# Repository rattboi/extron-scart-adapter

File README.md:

Extron Scart Adapter projects
=============================

Extron Input Adapter
--------------------

[Extron-Input README](extron-input/README.md)

This board should plug into an extron crosspoint input, and has the following features:

1) Female Scart input
1) JST header to Phoenix adapter (cheap)
1) Sense header to determine if connected cable is "active"
1) Selectable LM1881 Sync Stripper for sync on composite video / sync on luma

Extron Output Adapter
--------------------

[Extron-Output README](extron-output/README.md)

This board should plug into an extron crosspoint output, and has the following features:

1) Female Scart output
1) JST header to Phoenix adapter (cheap)
1) Selectable termination resistor for 75 ohm or TTL level sync output

Extron SCART Autoswitcher
-------------------------

[Autoswitcher README](esp32-switcher/README.md)

This board plugs into the serial port on an Extron crosspoint, and works together with the input cards to determine which input has be most-recently powered on, and automatically switches to that input.

Simple Scart Adapter (DEPRECATED)
---------------------------------

This board was my first attempt, and it turned out to not be workable. I'm leaving it for posterity, but you shouldn't use it.
The spacing is way off for a Crosspoint. I based the measurements on an Extron System 5CR Plus, which has narrower spacing between BNC connectors.

License
-------

These projects are licensed under CERN Open Hardware Licence v1.2

This is a work-in-progress as well, as I believe I'm missing the attribution on the boards. My intent is to license them properly.

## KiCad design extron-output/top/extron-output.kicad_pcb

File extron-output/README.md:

Extron SCART Output Adapter
==========================

PCB Renders
===========

## Front

## Back

3D Renders
==========

## Top

## Front

## Side

BOM 
===

| Item | Qty | Reference(s)     | Value      | Footprint                                                   | Datasheet                                                                                                            |
|------|-----|------------------|------------|-------------------------------------------------------------|----------------------------------------------------------------------------------------------------------------------|
| 1    | 1   | J1               | SCART-F    | extron-input:SCART_F_RA, ~                                  | https://console5.com/store/female-scart-jp21-through-hole-pcb-mount-21-pin-connector-right-angle.html                |
| 2    | 1   | J2/J11           | RED        | extron-input:rca_boom, ~                                    | https://lcsc.com/product-detail/AV-Connectors_AV-5_C18080.html                                                       |
| 3    | 1   | J3               | GREEN      | extron-input:rca_boom, ~                                    | https://lcsc.com/product-detail/AV-Connectors_AV-5_C18080.html                                                       |
| 4    | 1   | J4/J12           | BLUE       | extron-input:rca_boom, ~                                    | https://lcsc.com/product-detail/AV-Connectors_AV-5_C18080.html                                                       |
| 5    | 1   | J5/J13           | SYNC       | extron-input:rca_boom, ~                                    | https://lcsc.com/product-detail/AV-Connectors_AV-5_C18080.html                                                       |
| 6    | 1   | R1               | 470        | R_Axial_DIN0204_L3.6mm D1.6mm_P1.90mm_Vertical              | https://lcsc.com/product-detail/Metal-Film-Resistor-TH_470R-471-5_C176518.html                                       |
| 7    | 1   | J6               | PHOENIX    | Connector_JST:JST_XH_S03B XH-A_1x03_P2.50mm_Horizontal,~    | https://lcsc.com/product-detail/Wire-To-Board-Wire-To-Wire-Connector_JST-Sales-America_S3B-XH-A-LF-SN_JST-Sales-America-S3B-XH-A-LF-SN_C157928.html |
| 8    | 1   | SW1              | CSYNC      | 3x1 Pin Header                                              | (fill me in)                                                                                                         |

LCSC     Sub-total: __$6.76__ for everything for 10x boards (plus lots of spare parts)
Console5 Sub-total: __$14.90__ for RA Female SCART connectors
BOM Total: __$21.66__ for 10x boards

You'll want 5x of the top boards and 5x of the bottom boards
PCBs: __$4 for 5__ top, __$4 for 5__ bottom, plus $6 for slower shipping = __$14__

Total board Costs for 10: $21.66+14 = $35.66 =  $3.57 each (pretty cheap)

Other Supporting Parts 
======================

Phoenix adapter (for audio)
---------------------------

I've respun db_electronics' Phoenix RCA plug board to use JST headers: https://github.com/rattboi/phoenix-audio-adapter-kicad/tree/jst-xh/

$5 for 10x more boards on JLCPCB order, and $0.89 for JST headers

__$5.89__ for 10x populated boards = __$0.59 each__

JST cables (connect input audio to phoenix board)
----------
https://www.amazon.com/gp/product/B07HRMWVK9/

__$8 for 10__(need to find a better source)

BNC M to RCA M Plug Adapters
---------------
https://www.amazon.com/gp/product/B005C2KA88/

$5.39 for 10

__$21.56 for 40__ (4x per board, 10 boards)

Alternative: 

https://www.amazon.com/gp/product/B01H1A4QAQ/

$6.42 for 10

$25.68 for 40

10x board Total
===============
10x board + phoenix + cables + adapters: $36 + $6 + $8 + $22 = __~$72__

__$7.20 each, all parts, shipped__

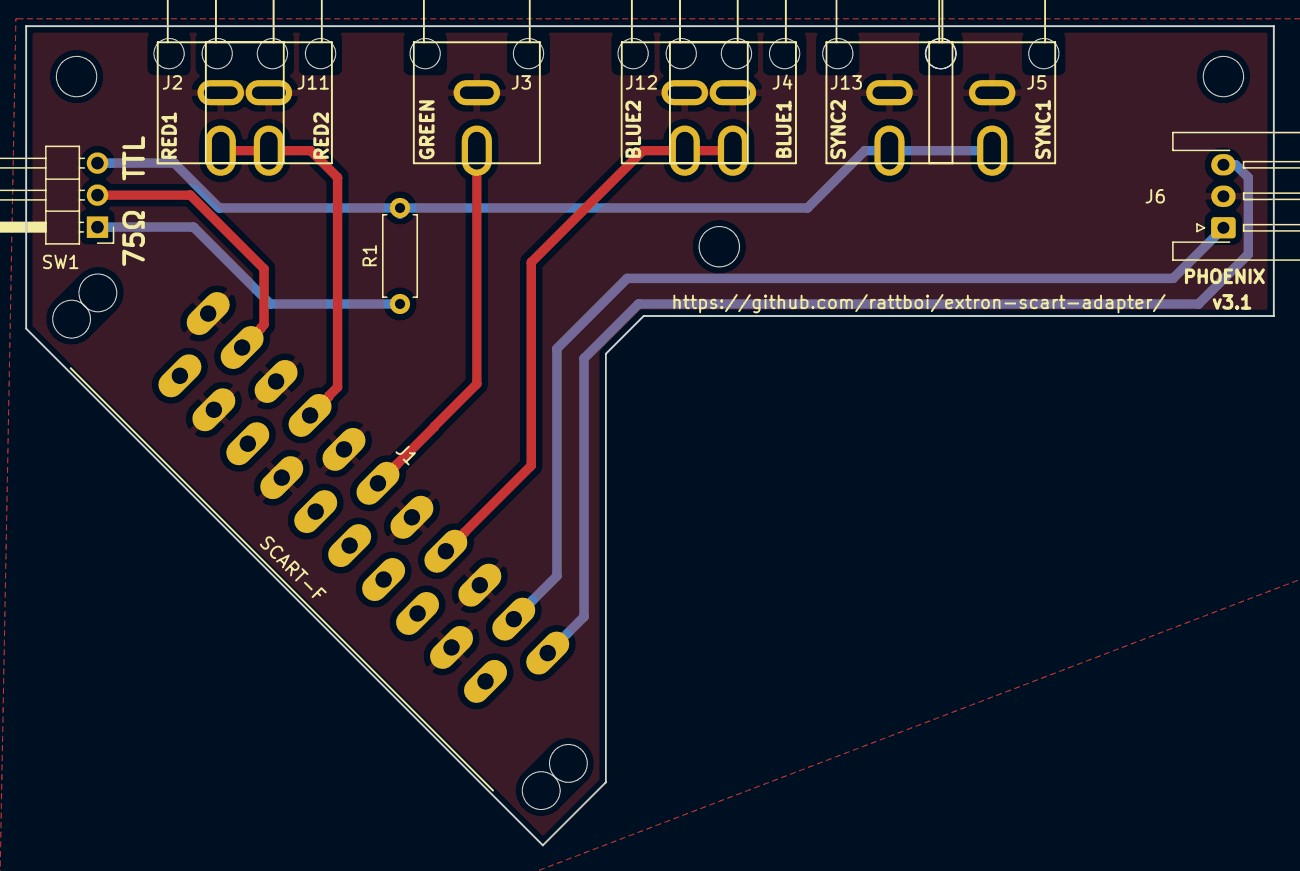
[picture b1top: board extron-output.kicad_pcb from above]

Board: 2 copper layers, 99.0 x 65.0 mm, 14 parts (0 on the bottom side), 9 nets.

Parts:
J1: SCART-F; SCART_F_RA
J2: RED1; rca_combined
J3: GREEN; rca_combined
J4: BLUE1; rca_combined
J5: SYNC1; rca_combined
J6: PHOENIX; JST_XH_S3B-XH-A-1_1x03_P2.50mm_Horizontal
J8, J9, J10: Conn_01x01; MountingHole_3.2mm_M3
J11: RED2; rca_combined
J12: BLUE2; rca_combined
J13: SYNC2; rca_combined
R1: 470; R_Axial_DIN0207_L6.3mm_D2.5mm_P7.62mm_Horizontal
SW1: SW_SPDT; PinHeader_1x03_P2.54mm_Horizontal

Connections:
BLUE: J1.7, J4.2, J12.2
GND: J1.4, J1.5, J1.9, J1.13, J1.14, J1.17, J1.18, J1.21, J2.1, J3.1, J4.1, J5.1, J6.2, J11.1, J12.1, J13.1
GREEN: J1.11, J3.2
unnamed: J1.1, J6.3
unnamed: J1.3, J6.1
unnamed: J1.19, SW1.2
unnamed: R1.1, SW1.1
RED: J1.15, J2.2, J11.2
SYNC: J5.2, J13.2, R1.2, SW1.3

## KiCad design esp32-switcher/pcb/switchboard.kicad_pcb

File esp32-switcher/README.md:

Extron SCART Autoswitcher
=========================

This board, in conjunction with a HiLetGo ESP-E32 development board, can be used to sense input changes from the Extron Input adapters, and use that information to automatically switch to the most recently turned-on input.

Each input board has a sense port, which you connect to the autoswitch board via a JST XH cable. The board then plugs into your extron either via straight-through M-F serial cable (not null modem), or by directly mounting the board onto the port. The ESP32 also needs external power, which can be supplied by any 5V USB charger that you may have laying around.

PCB
===

3D Renders
==========

PCB Renders
===========

BOM
===========
| Item  | Qty | Reference(s)     | Value      | Footprint                                                   | Datasheet                                                                                                            |
|-------|-----|------------------|------------|-------------------------------------------------------------|----------------------------------------------------------------------------------------------------------------------|
| 1     |   1 | U1               | ESP32      | hiletgo-e32:HILETGO-E32                                     |  https://www.amazon.com/gp/product/B0718T232Z/ref=ppx_yo_dt_b_search_asin_title?ie=UTF8&psc=1                        |
| 2     |   1 | J13/J16          | RS232      | Connector_PinSocket_2.54mm:PinSocket_1x04_P2.54mm_Vertical  |  https://www.amazon.com/gp/product/B00OPU2QJ4/ref=ppx_yo_dt_b_asin_title_o02_s00?ie=UTF8&psc=1                       |
| 3     |  14 | J1-12,14,15      | JST-XH RA  | Connector_JST:JST_XH_B2B-XH-AM_1x02_P2.50mm_Vertical        |                                                                                                                      |

Notes:
* You only need one RS232 TTL Converter. There's two spots (J13 or J16) on the board to place it, depending on what orientation you want your switchboard to be.
* You can skip J14/J15 for now. They are WIP to chain together switchboards for cascading multiple Extrons
* If you don't want the ESP32 to be permanently soldered to the switchboard, you can use pin header for the two rows of pins where the ESP32 plugs in.
* I would recommend directly soldering the RS232 in place for stability, but you could use pin header there as well.

Code
====

The code for the autoswitcher is currently in micropython. The basic steps involved are as follows to get the board going.

1) Install any driver you may need for the usb->serial built into the ESP32. This is the CP2102 driver, and necessary for Windows and macOS. Linux comes with this driver pre-installed.

2) Plug the ESP32 into your computer, and find the serial device.
  This is straightforward in Linux/macOS, as it appears as /dev/ttyUSB0 or something close to that. I'm not actually sure what this looks like in windows.

3) Install the following programs to interact with the ESP32: esptool.py and ampy.
  esptool.py will allow you to flash micropython onto your ESP32
  ampy will allow you to move the boot code from this repo onto your ESP32 to be executed by micropython

4) Install micropython, some current revision.
  I'm not going to go through all the steps for this, but on Linux it looks something like `sudo esptool --chip esp32 -p /dev/ttyUSB0 write_flash -z 0x1000 ~/Downloads/esp32-20190328-v1.10-243-g92149c8a7.bin`
  `
5) Move the boot code over after micropython is installed
  `ampy -p /dev/ttyUSB0 put code/boot.py`

You're done now. Plug everything in. J1 -> Input 1, J2 -> Input 2, etc.

Congrats, now you have autoswitching power!

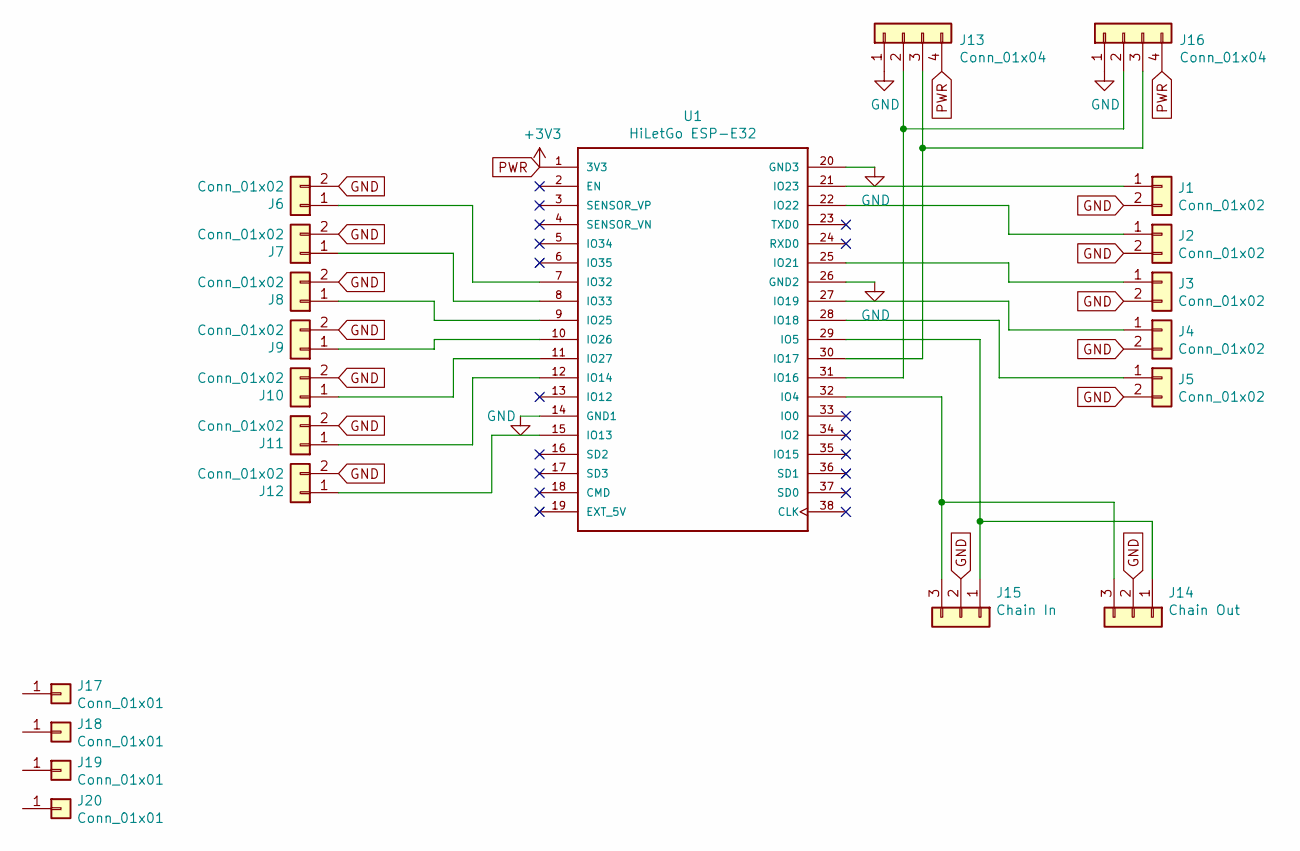
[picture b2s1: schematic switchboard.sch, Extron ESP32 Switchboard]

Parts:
J1, J2, J3, J4, J5, J6, J7, J8, J9, J10, J11, J12: Conn_01x02; JST_XH_B2B-XH-AM_1x02_P2.50mm_Vertical
J13, J16: Conn_01x04; PinSocket_1x04_P2.54mm_Vertical
J14: Chain Out; JST_XH_B3B-XH-AM_1x03_P2.50mm_Vertical
J15: Chain In; JST_XH_B3B-XH-AM_1x03_P2.50mm_Vertical
J17, J18, J19, J20: Conn_01x01; MountingHole_3.2mm_M3
U1: HiLetGo ESP-E32; HILETGO-E32

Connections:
GND: J1.2, J2.2, J3.2, J4.2, J5.2, J6.2, J7.2, J8.2, J9.2, J10.2, J11.2, J12.2, J13.1, J14.2, J15.2, J16.1, U1.14 (GND1), U1.20 (GND3), U1.26 (GND2)
unnamed: J1.1, U1.21 (IO23)
unnamed: J2.1, U1.22 (IO22)
unnamed: J3.1, U1.25 (IO21)
unnamed: J4.1, U1.27 (IO19)
unnamed: J5.1, U1.28 (IO18)
unnamed: J6.1, U1.7 (IO32)
unnamed: J7.1, U1.8 (IO33)
unnamed: J8.1, U1.9 (IO25)
unnamed: J9.1, U1.10 (IO26)
unnamed: J10.1, U1.11 (IO27)
unnamed: J11.1, U1.12 (IO14)
unnamed: J12.1, U1.15 (IO13)
unnamed: J13.2, J16.2, U1.31 (IO16)
unnamed: J13.3, J16.3, U1.30 (IO17)
unnamed: J14.1, J15.1, U1.29 (IO5)
unnamed: J14.3, J15.3, U1.32 (IO4)
PWR: J13.4, J16.4, U1.1 (3V3)

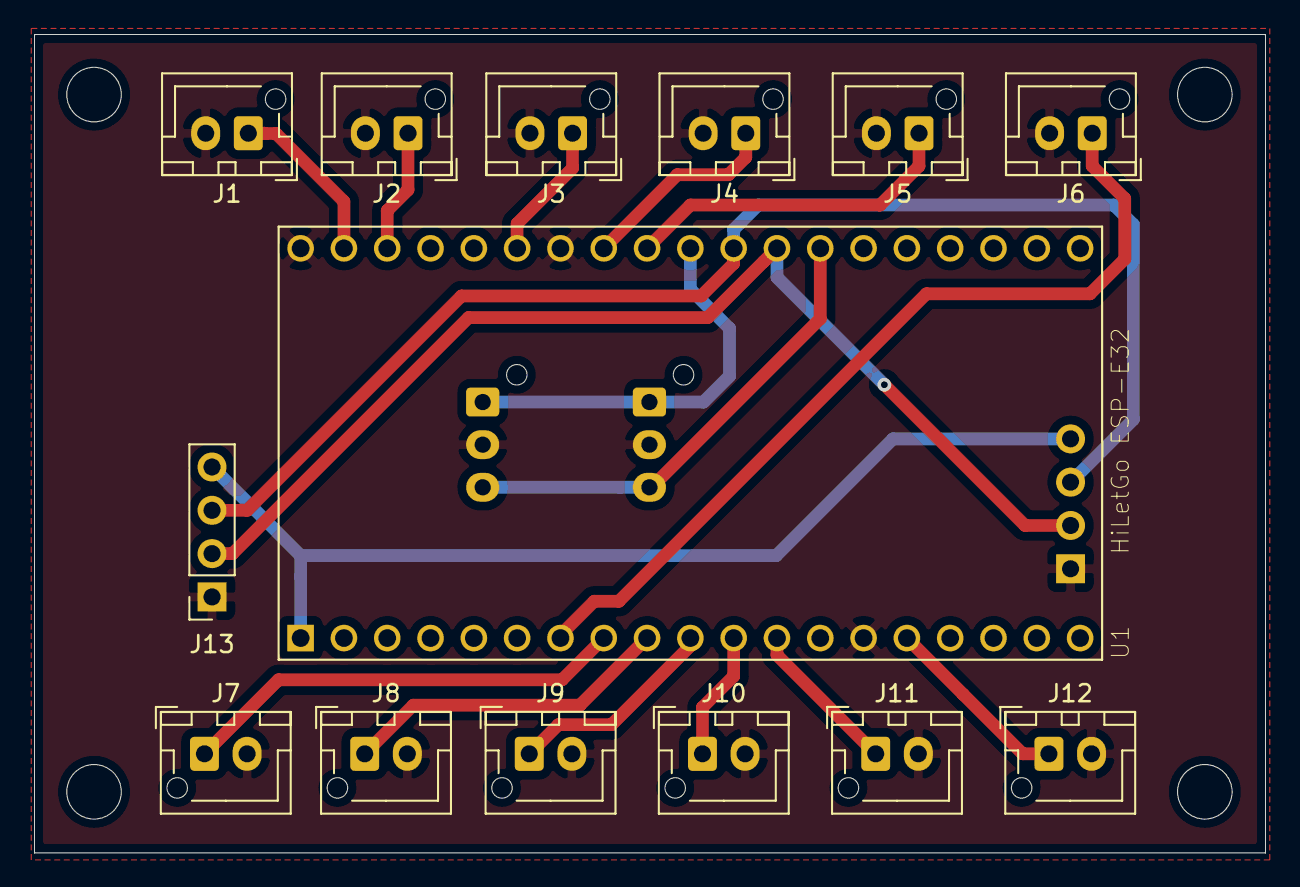
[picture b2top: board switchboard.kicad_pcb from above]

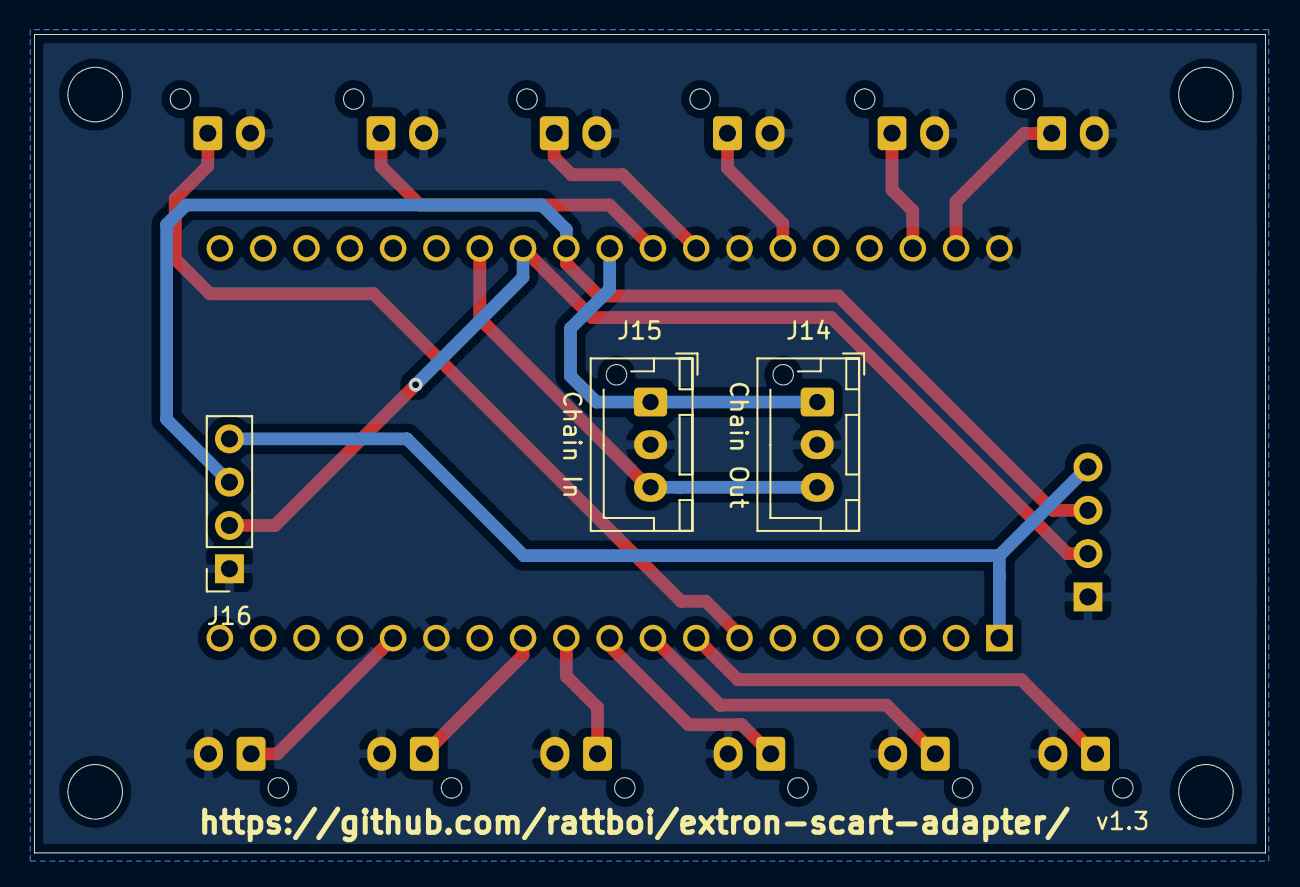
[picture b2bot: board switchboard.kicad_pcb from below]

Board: 2 copper layers, 72.2 x 48.0 mm, 21 parts (3 on the bottom side), 18 nets.

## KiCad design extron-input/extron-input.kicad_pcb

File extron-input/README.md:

Extron SCART Input adapter
==========================

The Extron SCART Input adapters are designed to be inserted into an Extron Crosspoint input vertically, using BNC->RCA male adapters to mate with the adapter card's RCA female jacks. There are two supported BNC spacings, one that is looser (older Extrons) and one that is tighter (newer Extrons). When you assemble your card, you use the correct RCA spacing to support your Extron. The looser spacing is labeled RED1/GREEN/BLUE1/SYNC1, while the tighter spacing is labeled RED2/GREEN/BLUE2/SYNC2. You'll notice that GREEN is shared between the two spacings.

Below, you will notice that there is a design for a 'top' card and a 'bottom' card. This was required in order to get the cards close enough together horizontally (from the perspective of the Extron). The SCART heads are large and for the newer Extron spacing, the BNC spacing is just too tight to have the SCART heads stack. Therefore, you should plan to make both 'top' and 'bottom' cards, and alternate them. I use plastic standoffs to group 3-4 boards together. For the newer Extrons, I found that alternating 15mm and 16mm standoffs gave a perfect fit. Anothe alternative would be to just pair up a top and bottom board, and use either 15mm or 16mm. The error builds when you try to create a larger matrix, so you shouldn't have any problem if you make smaller matrices.

Features
========

The Extron input cards have optional sync strippers that are togglable via a switch that is labeled on the PCB. The lm1881 sync stripper is powered by the SCART cable's pin 8 (switch pin). The SCART standard says that this should be carrying 5v-12v. Anywhere in that range works fine to power the lm1881.

Also, there is a small custom circuit to determine if the console is powered on, via the switch pin on the SCART connector. This can be paired with the [autoswitcher](../esp32-switcher) to automatically switch the extron input to match the last powered-on device. This circuit takes 5-12V and lowers it down to 2.5-3.3V, which is low enough to be a simple digital 'on' signal to the [autoswitcher](../esp32-switcher) board.

PCB Renders
===========

## Front

## Back

3D Renders
==========

## Top

## Front

## Side

Assembled Cards
===============

Others
======

BOM
===========
| Item | Qty | Reference(s)     | Value      | Footprint                                                   | Datasheet                                                                                                            |
|------|-----|------------------|------------|-------------------------------------------------------------|----------------------------------------------------------------------------------------------------------------------|
| 1    | 2   | C1, C2           | 0.1uF      | Capacitor_THT:C_Disc_D3.0mm W1.6mm_P2.50mm                  | https://lcsc.com/product-detail/Multilayer-Ceramic-Capacitors-MLCC-Leaded_100nF-104-20-100V_C154503.html             |
| 2    | 1   | D1               | 1N4148     | Diode_THT:D_DO-35_SOD27 P2.54mm_Vertical_AnodeUp            | https://lcsc.com/product-detail/Switching-Diode_1N4148_C14516.html                                                   |
| 3    | 1   | D2               | 1N4728A    | Diode_THT:D_DO-35_SOD27 P2.54mm_Vertical_AnodeUp,~          | https://lcsc.com/product-detail/Zener-Diodes_ON-Semicon_1N4728A_ON-Semicon-ON-1N4728A_C140852.html                   |
| 4    | 1   | J1               | SCART-F    | extron-input:SCART_F_RA, ~                                  | https://console5.com/store/female-scart-jp21-through-hole-pcb-mount-21-pin-connector-right-angle.html                |
| 5    | 1   | J2/J11           | RED        | extron-input:rca_boom, ~                                    | https://lcsc.com/product-detail/AV-Connectors_AV-5_C18080.html                                                       |
| 6    | 1   | J3               | GREEN      | extron-input:rca_boom, ~                                    | https://lcsc.com/product-detail/AV-Connectors_AV-5_C18080.html                                                       |
| 7    | 1   | J4/J12           | BLUE       | extron-input:rca_boom, ~                                    | https://lcsc.com/product-detail/AV-Connectors_AV-5_C18080.html                                                       |
| 8    | 1   | J5/J13           | SYNC       | extron-input:rca_boom, ~                                    | https://lcsc.com/product-detail/AV-Connectors_AV-5_C18080.html                                                       |
| 9    | 1   | J6               | PHOENIX    | Connector_JST:JST_XH_S03B XH-A_1x03_P2.50mm_Horizontal,~    | https://lcsc.com/product-detail/XH-Connectors_JST_S3B-XH-A-LF-SN_XHsocket-1-3P-Curved-needle-pitch2-5mm_C157928.html |
| 10   | 1   | J7               | SENSE      | Connector_JST:JST_XH_S02B XH-A_1x02_P2.50mm_Horizontal,~    | https://lcsc.com/product-detail/XH-Connectors_JST_S2B-XH-A-LF-SN_XHsocket-1-2P-Curved-needle-pitch2-5mm_C157931.html |
| 11   | 4   | J8, J9, J10, J11 | Conn_01x01 | MountingHole:MountingHole_3.2mm_M3                          | N/A                                                                                                                  |
| 12   | 1   | R1               | 680KΩ      | Resistor_THT:R_Axial_DIN0204 L3.6mm_D1.6mm_P1.90mm_Vertical | https://lcsc.com/product-detail/Others_FlyWin-CR1-8W-5-680K-OTB5_C337028.html                                        |
| 13   | 1   | R2               | 100Ω       | Resistor_THT:R_Axial_DIN0204 L3.6mm_D1.6mm_P1.90mm_Vertical | https://www.lcsc.com/product-detail/Through-Hole-Resistors_CCO-Chian-Chia-Elec-CF1-4W-100-5-T52_C120031.html                                       |
| 14   | 1   | R3               | 1KΩ        | Resistor_THT:R_Axial_DIN0204 L3.6mm_D1.6mm_P1.90mm_Vertical | https://lcsc.com/product-detail/Carbon-Film-Resistors_1KR-102-5_C120055.html                                         |
| 15   | 1   | SW1              | SW_DPDT_x2 | Button_Switch_THT:SW_CuK JS202011AQN_DPDT_Angled,           | https://lcsc.com/product-detail/Toggle-Switches_C-K_JS202011AQN_C-K-JS202011AQN_C221662.html                         |
| 16   | 1   | U1               | LM1881     | Package_DIP:DIP-8_W7.62mm,                                  | https://www.ti.com/store/ti/en/p/product/?p=LM1881N/NOPB

LCSC     Sub-total: __$14.94__ for everything for 10x boards (plus lots of spare parts)

Console5 Sub-total: __$14.90__ for RA Female SCART connectors

TI       Sub-total: __$28.40__ for LM1881n 

BOM Total for 10x boards: __$58.40__ plus Console5/TI shipping

BOM Total with shipping: __~$70__

You'll want 5x of the top boards and 5x of the bottom boards
PCBs: __$4 for 5__ top, __$4 for 5__ bottom, plus $6 for slower shipping = __$14__

Cost for 10 boards, all parts: $70+14 = $84 = __$8.40__ each

Other Supporting Parts 
======================

Phoenix adapter (for audio)
---------------------------

I've respun db_electronics' Phoenix RCA plug board to use JST headers: https://github.com/rattboi/phoenix-audio-adapter-kicad/tree/jst-xh/

$5 for 10x more boards on JLCPCB order, and $0.89 for JST headers

__$5.89__ for 10x populated boards = __$0.59 each__

JST cables (connect input audio to phoenix board)
----------
https://www.amazon.com/gp/product/B07HRMWVK9/

__$8 for 10__(need to find a better source)

BNC M to RCA M Plug Adapters
---------------
https://www.amazon.com/gp/product/B005C2KA88/

$5.39 for 10

__$21.56 for 40__ (4x per board, 10 boards)

Alternative: 

https://www.amazon.com/gp/product/B01H1A4QAQ/

$6.42 for 10

$25.68 for 40

10x board Total
===============
10x board + phoenix + cables + adapters: $84 + $6 + $8 + $22 = __~$120__

__$12 each, all parts, shipped__

10x boards Stripped-down 
------------------------

If you were to remove the optional components (no sync stripper, no sense circuit), you can get the price down further

Removing switch + lm1881 and passives for lm1881 + passives for sense circuit + sense connector: 

LCSC     Sub-total: $7.06

Console5 Sub-total: $14.90 for SCART connectors

BOM Total with shipping: $7.06 + $14.90 + $5 = $27

PCBS are the same, so $14 for 10x boards shipped

The rest of the parts are the same

10x board + phoenix + cables + adapters: $41 + $3 + $8 + $23 = __~$75__

__$7.50 each, stripped-down, shipped__

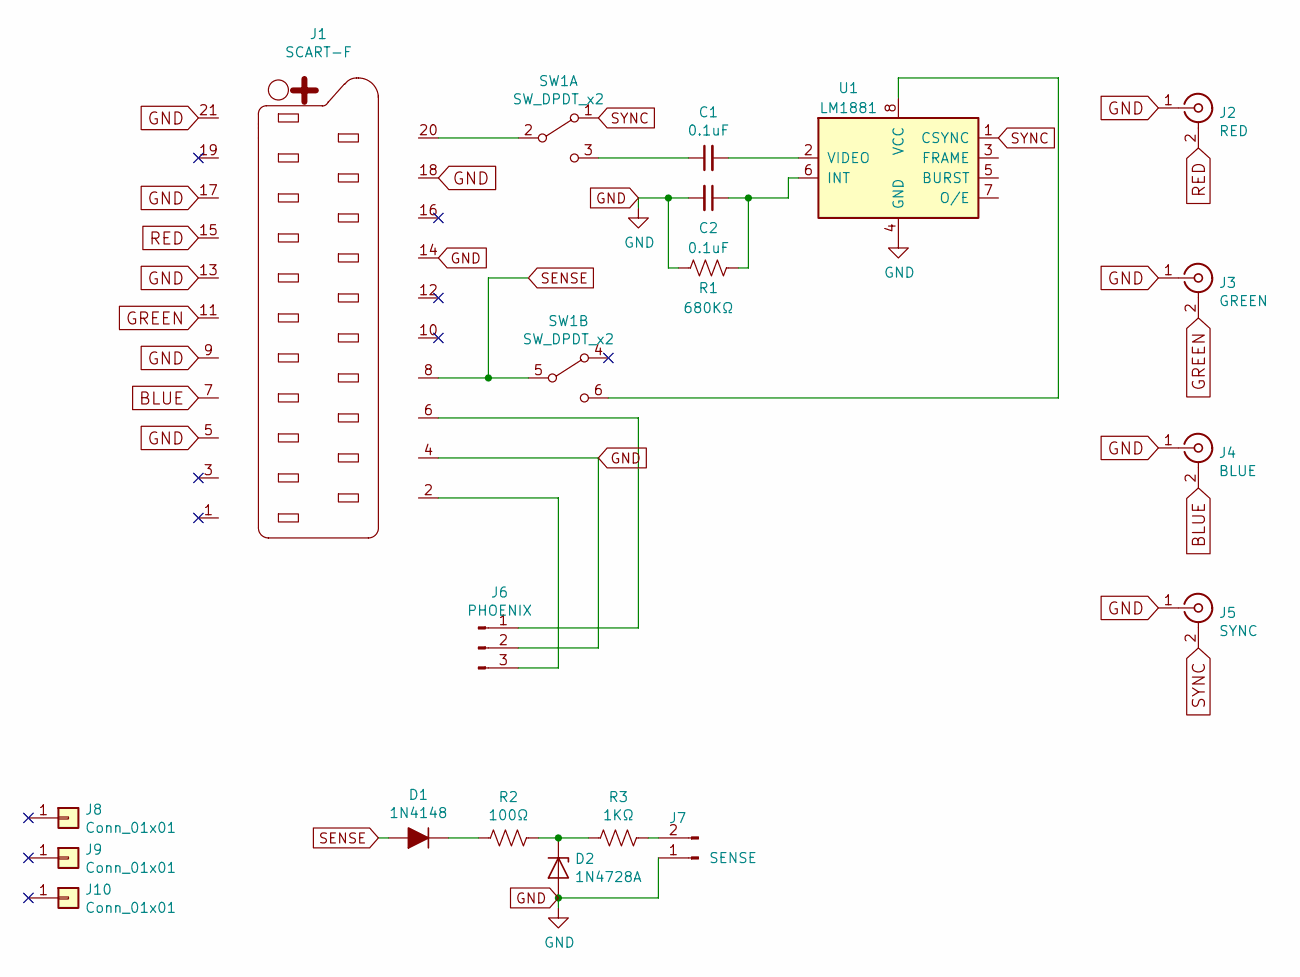
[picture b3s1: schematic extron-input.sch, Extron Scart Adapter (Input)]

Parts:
C1, C2: 0.1uF; C_Disc_D3.0mm_W1.6mm_P2.50mm
D1: 1N4148; D_DO-35_SOD27_P2.54mm_Vertical_AnodeUp
D2: 1N4728A; D_DO-35_SOD27_P2.54mm_Vertical_AnodeUp
J1: SCART-F; SCART_F_RA
J2: RED; rca_combined
J3: GREEN; rca_combined
J4: BLUE; rca_combined
J5: SYNC; rca_combined
J6: PHOENIX; JST_XH_S3B-XH-A-1_1x03_P2.50mm_Horizontal
J7: SENSE; JST_XH_S2B-XH-A_1x02_P2.50mm_Horizontal
J8, J9, J10: Conn_01x01; MountingHole_3.2mm_M3
R1: 680KΩ; R_Axial_DIN0204_L3.6mm_D1.6mm_P1.90mm_Vertical
R2: 100Ω; R_Axial_DIN0204_L3.6mm_D1.6mm_P1.90mm_Vertical
R3: 1KΩ; R_Axial_DIN0204_L3.6mm_D1.6mm_P1.90mm_Vertical
SW1: SW_DPDT_x2; SW_CuK_JS202011AQN_DPDT_Angled
U1: LM1881; DIP-8_W7.62mm

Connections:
BLUE: J1.7, J4.2 (Ext)
GND: C2.2, D2.2 (A), J1.4, J1.5, J1.9, J1.13, J1.14, J1.17, J1.18, J1.21, J2.1 (In), J3.1 (In), J4.1 (In), J5.1 (In), J6.2, J7.1, R1.1, U1.4 (GND)
GREEN: J1.11, J3.2 (Ext)
unnamed: C1.1, SW1.3 (C)
unnamed: C1.2, U1.2 (VIDEO)
unnamed: C2.1, R1.2, U1.6 (INT)
unnamed: D1.1 (K), R2.2
unnamed: D2.1 (K), R2.1, R3.2
unnamed: J1.2, J6.3
unnamed: J1.6, J6.1
unnamed: J1.20, SW1.2 (B)
unnamed: J7.2, R3.1
unnamed: SW1.6 (C), U1.8 (VCC)
RED: J1.15, J2.2 (Ext)
SENSE: D1.2 (A), J1.8, SW1.5 (B)
SYNC: J5.2 (Ext), SW1.1 (A), U1.1 (CSYNC)

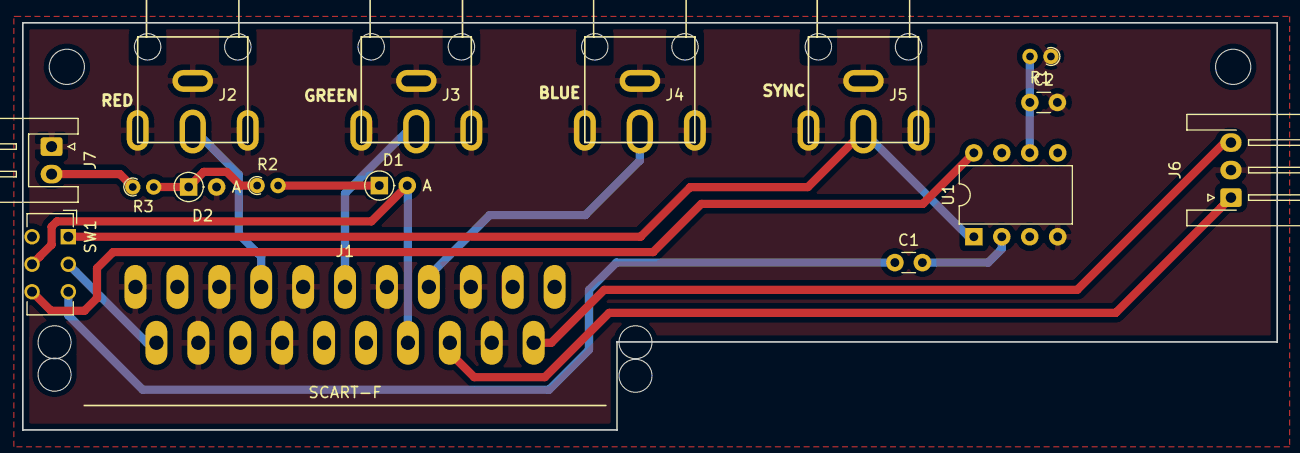
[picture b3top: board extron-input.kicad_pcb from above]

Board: 2 copper layers, 114.0 x 37.0 mm, 18 parts (0 on the bottom side), 16 nets.

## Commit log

2019-02-10 First commit. Just some ideas.
2019-02-14 First test. Sent off to OSHPark.
    Based off Arithmaldor's SCART-to-RCA project. Thanks, buddy.
2019-02-14 Adding renders, cleaned up readme a bit
2019-02-27 New sch/pcb input from extron crosspoint dimensions
    Different orientation for the board
    Added selectable sync stripper
    Missing mounting holes, and better silkscreen, but mostly done
2019-02-27 Remove unused schematic libs
2019-02-27 V1.0 -> Sent to JLCPCB
    Hopefully everything is right
2019-02-27 Adding new renders for Crosspoint input version
2019-02-27 Move to subdir, make fakey readme
2019-02-27 Move old proj to scart-simple (deprecated)
2019-02-27 Remove README. It's been moved into scart-simple
2019-02-27 Attempt to table-ize the bom
2019-02-27 More fleshed-out readme. Still needs work
2019-02-27 Trying to make the BOM more readable
2019-02-28 Add 3d renders for input board
2019-02-28 More table fixes
2019-02-28 Rename things to scart-input
2019-02-28 Remove gerbers zip
2019-02-28 Oops, scart-input -> extron-input
2019-02-28 Make sure that it's obvious the simple-scart deprecated
2019-02-28 Add new Extron Output board. Need to fix readme to reflect
2019-02-28 Adding fixed render (I think)
2019-02-28 Added updated Readme
2019-02-28 Adding license and base readme for projects
2019-02-28 Fix resistor value in BOM for input adapter
2019-02-28 Random fixes to extron-input layout/schematic
    There were some weirdnesses between the schematic and layout. I believe
    these are fixed now.
    I also switched the footprint to JST XH side connectors for both sense
    and phoenix ports. I found that there are cables that can be purchased
    for cheap for this form factor.
2019-02-28 Forgot to reflow the ground planes after making adjustments
2019-02-28 Update BOM with XH side connectors
2019-03-10 Rev 2 input board (+ other small things)
    BNC F -> RCA F for all outputs to extron
    The BNC is great, but expensive, and also impossible to close over an
    extron input when they are matrixed. The RCA female recepticles will
    all to use with RCA M -> BNC M adapters, which you can pre-load onto
    the extron BNC F inputs. This will allow cards to plug in
    individually, or all at once if you have a stack of cards held
2019-03-10 Update readme to show out-of-date, rca too thicc
2019-03-10 Redo renders, fix RCA 3d model reference
2019-03-10 Added vendor/link to all schematic parts
2019-03-10 Updated BOM in input card readme
2019-03-10 More BOM fixes
2019-03-10 Updated readme with latest cost breakdown
2019-03-10 Fixed some formatting
2019-03-10 More formatting fixes (spacing is important)
2019-03-10 Updated price breakdown math, link to phoenix respin
2019-03-28 Rev 2.1
    Fixed up rca problems by making combined footprint for the two different
    CUI-style connectors.
    Shifted scart over so it doesn't run into standoffs (hopefully)
    Fixed resistor value in sense circuit
    Reversed stereo audio signals
    Added logos + link to site
2019-03-28 Adding in missing "rescue" files.
2019-03-28 Added new pcb renders (2d, at least)
2019-04-01 WIP esp32-switchboard + esp32 micropython code
2019-04-01 Updates, almost ready to go
2019-04-05 Rev 1.1 of ESP32 Switchboard
    I think this rev is basically ready to go. I could see someone using
    this for real. I still have a lot of software features I wanna add, but
    the hardware is basically complete.
    I may come back and add a built-in serial port, as the little breakout
    can be flimsy, but it seems that 3v3 rs232 stuff means SMD components,
    and I've been trying to avoid that to make this easier to DIY.
2019-04-05 Rearranged files, updated docs. Hopefully ready to merge
2019-04-05 Fix switchboard renders
2019-04-13 Update extron output board to use combined RCA (v2.1)
    Small fixes for extron input as well (v2.1)
2019-04-13 Switchboard v1.2
    Switch around all the XA connectors to allow for either top-entry or
    side-entry XH connectors.
2019-04-15 Add mounting holes and 2nd position for serial uart on switchboard
    Also, "rescue" components on scart-input board. I gotta figure out what
    that's about...
2019-05-22 Version 2.2 of extron input (move sense to top)
    This revision moves the sense circuit to the top of the board, which
    makes the audio plug a lot easier to get at, and you can throw your
    esp32-switcher on the top of your extron.
    Also cleaned up rescue files for eeschema. Come on, eeschema. Get your
    shit together.
2019-05-22 Fixup references from schematic -> pcb
2019-05-22 Fix 3d-top render for extron-input v2.2
2019-06-01 WIP on input board v3
    New features:
    Longer boards that support top/bottom placement, allowing closer
    placement for extron 300 ADSP models, and allowing thicker FR4 again
    Will have new RCA placements to support both older and newer extron
    BNC spacings
2019-06-01 WIP v3 (more)
    * Made separate top/bottom directories (only top for now)
    * Made symlinks to keep one schematic for two pcbs
    * Modified "rca_combined" to no longer be combined. We're going w/ the rca
    boom from lcsc.
    * Doubled up footprints for R / B / Sync to support both new and old
    extron crosspoints
2019-06-01 Added bottom board
    Looks like I need to fix the schematic being in multiple places...
2019-06-07 Changed top to 45 degree scart insertion
    * totally new concept here for me. I'm not super happy with the routing,
    but I am more concerned about the mechanical layout right now, honestly.
    I'm hoping that the track width being fairly wide will help the crap
    routing.
2019-06-08 Bottom board is now done(ish)
    I've also aligned the mounting holes between the boards
2019-06-10 Found a size for the bottom board that won't impede on the top board
    These prototypes are sent off to JLC, so I'm also capturing the gerbers
    in the repo.
    V3.1pre
    I think these have a good chance to be good...
2019-06-25 extron-input v3
    Extended bottom board by 5mm
    Fixed silkscreen up to be reasonable
    Fixed up gitignore
2019-07-15 WIP top output board
    Still need to clean up base output directory. Will happend when bottom
    output board is done.
2019-07-15 Add bottom output board
2019-07-15 Cleanup towards better top/bottom output board file hierarchy
2019-07-29 Updated renders and added a bit more docs for input cards
2019-07-29 Add a bit of extron-output readme update (renders)
2019-07-29 Fix bottom 3d side render
2019-07-29 New layout renders
2019-07-29 More readme fixes
2019-07-29 More readme
2019-07-29 Redo renders, update PCB 3d models for side connectors
    Remove ropeproject, add gitignore to stop adding in the future
2019-08-03 More documentation/images
2019-08-04 Update some images, move traces to make ground flood better
2019-08-04 Replace renders with new top/bottom renders
2019-08-04 Updated extron output readme to reflect correct BOM + prices
2019-08-04 Version 3.1 (#6)
    * WIP on input board v3
    New features:
    Longer boards that support top/bottom placement, allowing closer
    placement for extron 300 ADSP models, and allowing thicker FR4 again
    Will have new RCA placements to support both older and newer extron
    BNC spacings
2019-08-09 Update renders for autoswitch board
    Add multi-output (still hardcoded, but it's a start)
    Naming refactors
2019-09-19 Adding BOM for Switchboard
2020-01-31 Fix errors about KiCad version
    I was using a nightly build of Kicad and some of those changes didn't
    end up making it into the main release. Now you should be able to just
    get latest Kicad and open all the files.
2020-01-31 Fix errors about KiCad version (#8)
    I was using a nightly build of Kicad and some of those changes didn't
    end up making it into the main release. Now you should be able to just
    get latest Kicad and open all the files.
2021-09-07 Fix R2 in BOM
    Was right in the schematic, but missed updating the bom :(
